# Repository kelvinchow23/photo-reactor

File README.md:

# Photoreactor Rev B

An update to the [AC-SDL4 photo-reactor](https://github.com/AC-SDL4/photo-reactor)
using custom PCBs for a four-reactor controller and interchangeable LED/fan boards.

The **photoreactor project is Rev B**. Both PCB parts remain **Rev A**:
SDL4-0001 photoreactor-controller and SDL4-0002 photoreactor-led.

- [PCB designs, BOMs, Gerbers and STEP models](electrical/README.md)
- [MicroPython test programs](firmware/README.md)
- [Wiring diagram](electrical/docs/wiring/photoreactor-wiring.pdf)
- [DigiKey import list](electrical/outputs/procurement/2026-10-15/DigiKey-bulk-import.txt)
- [Housing development](mechanical/housing/README.md)

Prototype bring-up is in progress; see [bench results](docs/bench-results.md).
Housing CAD will be added later.

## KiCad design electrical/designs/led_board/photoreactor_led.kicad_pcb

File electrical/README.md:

# Custom PCBs

PCB parts for the **Photoreactor Rev B** project. Both physical PCB revisions are
**Rev A**, dated 2026-10-08.

| Part | Native KiCad project | Fabrication and assembly files |
| --- | --- | --- |
| SDL4-0001 photoreactor-controller | [Open project](designs/controller/photoreactor_quad.kicad_pro) | [Rev A package](outputs/controller/SDL4-0001_photoreactor-controller_Rev-A_2026-10-08/) |
| SDL4-0002 photoreactor-led | [Open project](designs/led_board/photoreactor_led.kicad_pro) | [Rev A package](outputs/led_board/SDL4-0002_photoreactor-led_Rev-A_2026-10-08/) |

The controller serves four reactors. Each reactor uses two identical LED/fan
boards, linked by a custom harness. Native schematics and layouts are the design
sources; libraries are shared under `libraries/`.

## Useful files

- [Wiring diagram](docs/wiring/photoreactor-wiring.pdf) and [editable draw.io file](docs/wiring/photoreactor-wiring.drawio)
- [Controller assembly BOM](outputs/controller/SDL4-0001_photoreactor-controller_Rev-A_2026-10-08/SDL4-0001_photoreactor-controller_Rev-A_2026-10-08_BOM.csv)
- [LED-board assembly BOM](outputs/led_board/SDL4-0002_photoreactor-led_Rev-A_2026-10-08/SDL4-0002_photoreactor-led_Rev-A_2026-10-08_BOM.csv)
- [DigiKey bulk-import list](outputs/procurement/2026-10-15/DigiKey-bulk-import.txt) and [shopping guide](outputs/procurement/2026-10-15/shopping-guide.html)
- [Mechanical STEP assemblies and previews](outputs/mechanical/Rev-A/SDL4_REV_A_mechanical-models.zip)
- [Thermal guidance](docs/THERMAL_PLAN.md)
- [Bench test firmware](../firmware/README.md) and [observed results](../docs/bench-results.md)

Heatsink contact area is included in the LED mechanical model. Component envelopes
are simplified and mating plugs/wire bends require additional clearance.

## Maintenance

Helper code belongs in [automation](automation/README.md), not in design folders.
Test/export commands preserve native PCB geometry. Validation outputs go to a
separate ignored folder; existing Rev A manufacturing packages are not overwritten.

This is a functionally exercised prototype, not a thermally qualified design.

## Output naming

Release folders and deliverable filenames use
`<part-number>_<part-name>_Rev-<revision>_<YYYY-MM-DD>`, followed by the
file purpose, such as `_Gerbers.zip`, `_BOM.csv`, `_CPL.csv` or `_board-only.step`.
The date records completion of that PCB release; it is not the date of a later
file rename or documentation update. Current PCB releases were completed 2026-10-08.
Native design files and the Gerber filenames inside the fabrication ZIPs retain
their original names.

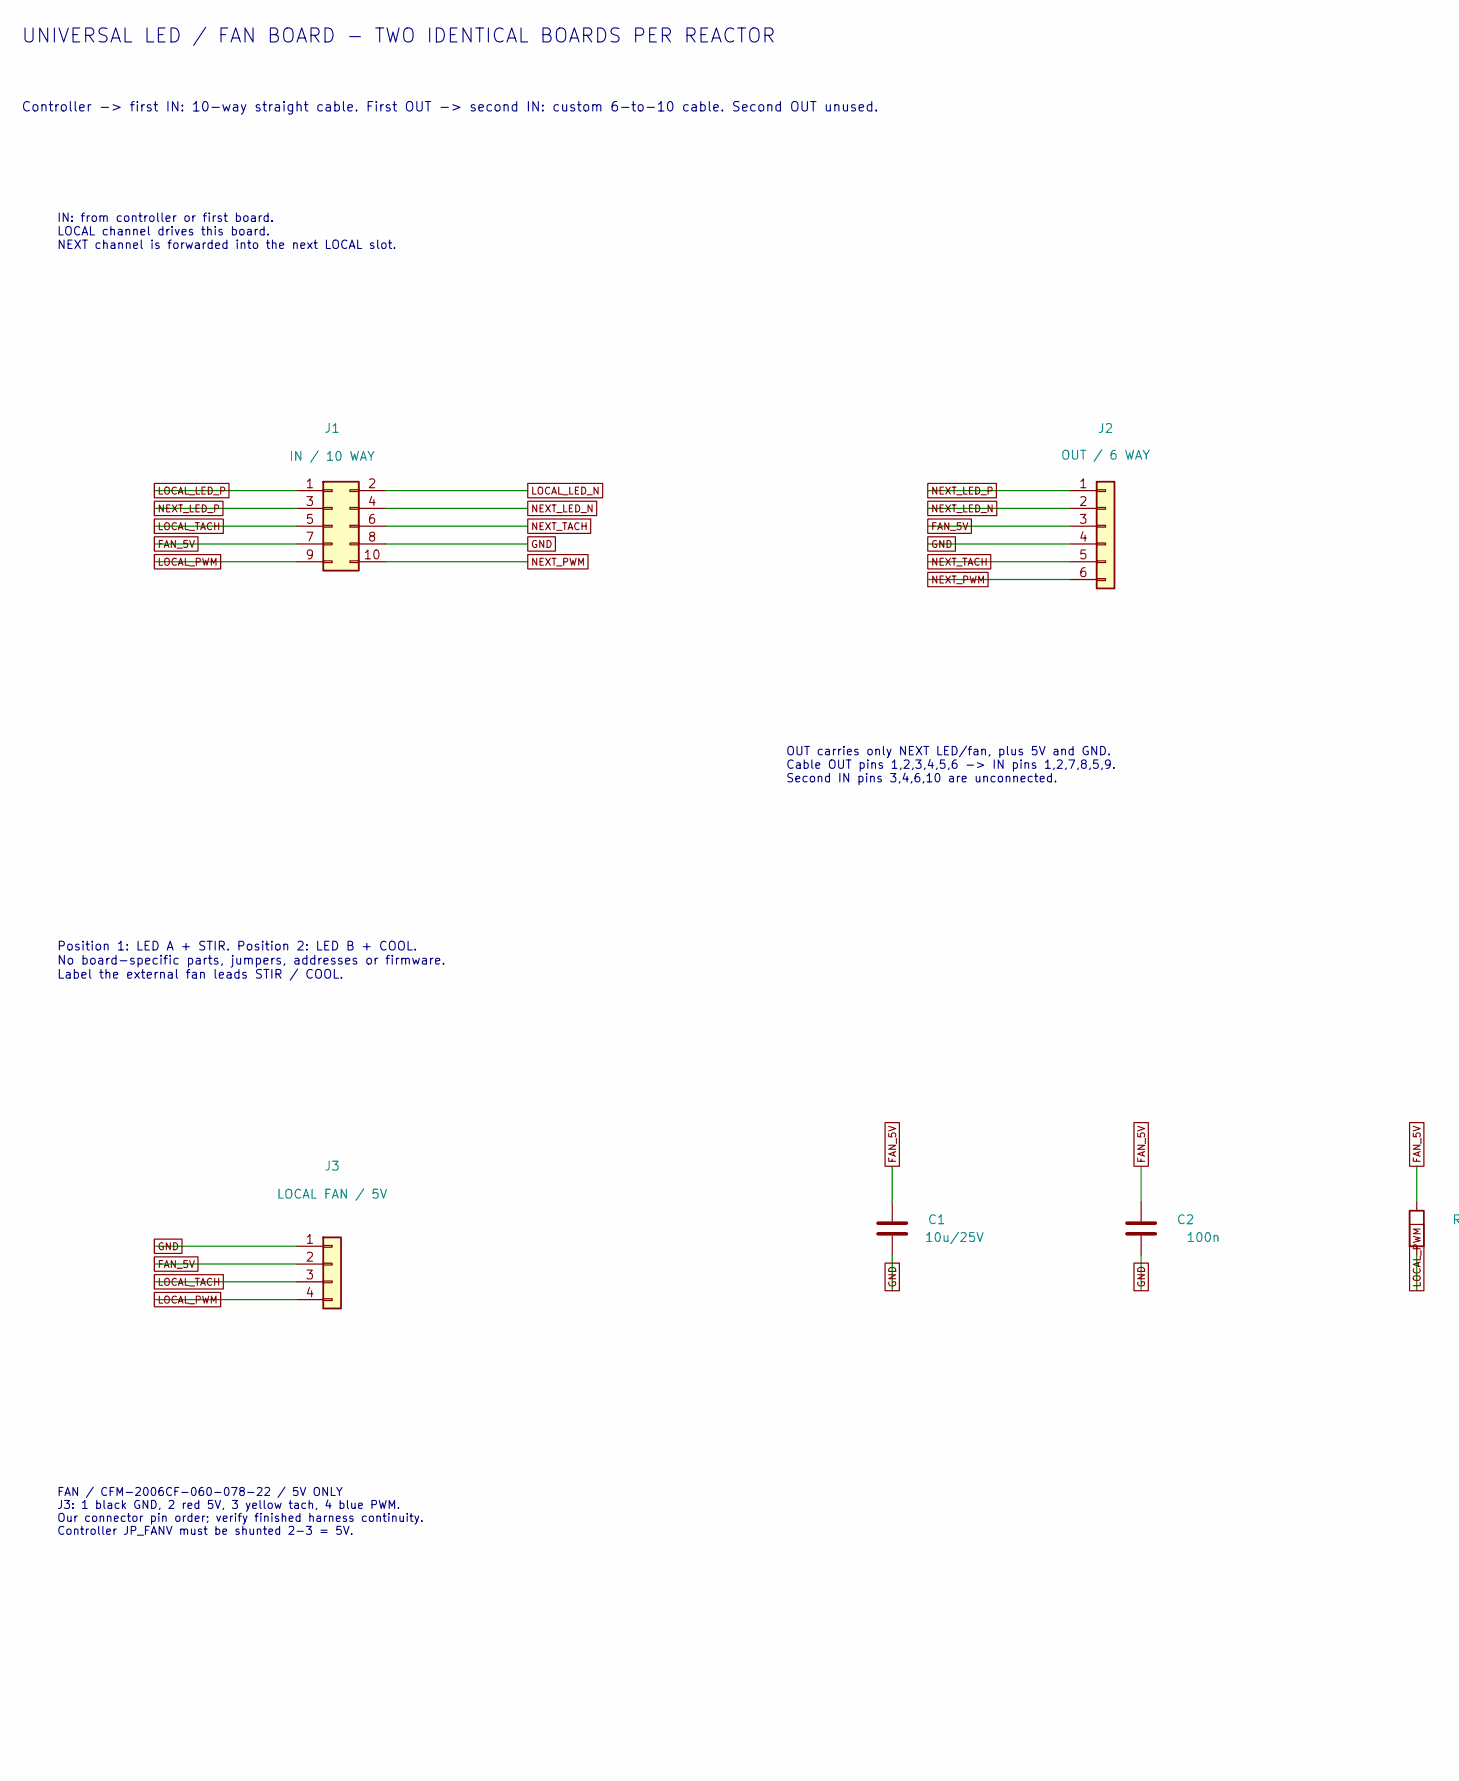
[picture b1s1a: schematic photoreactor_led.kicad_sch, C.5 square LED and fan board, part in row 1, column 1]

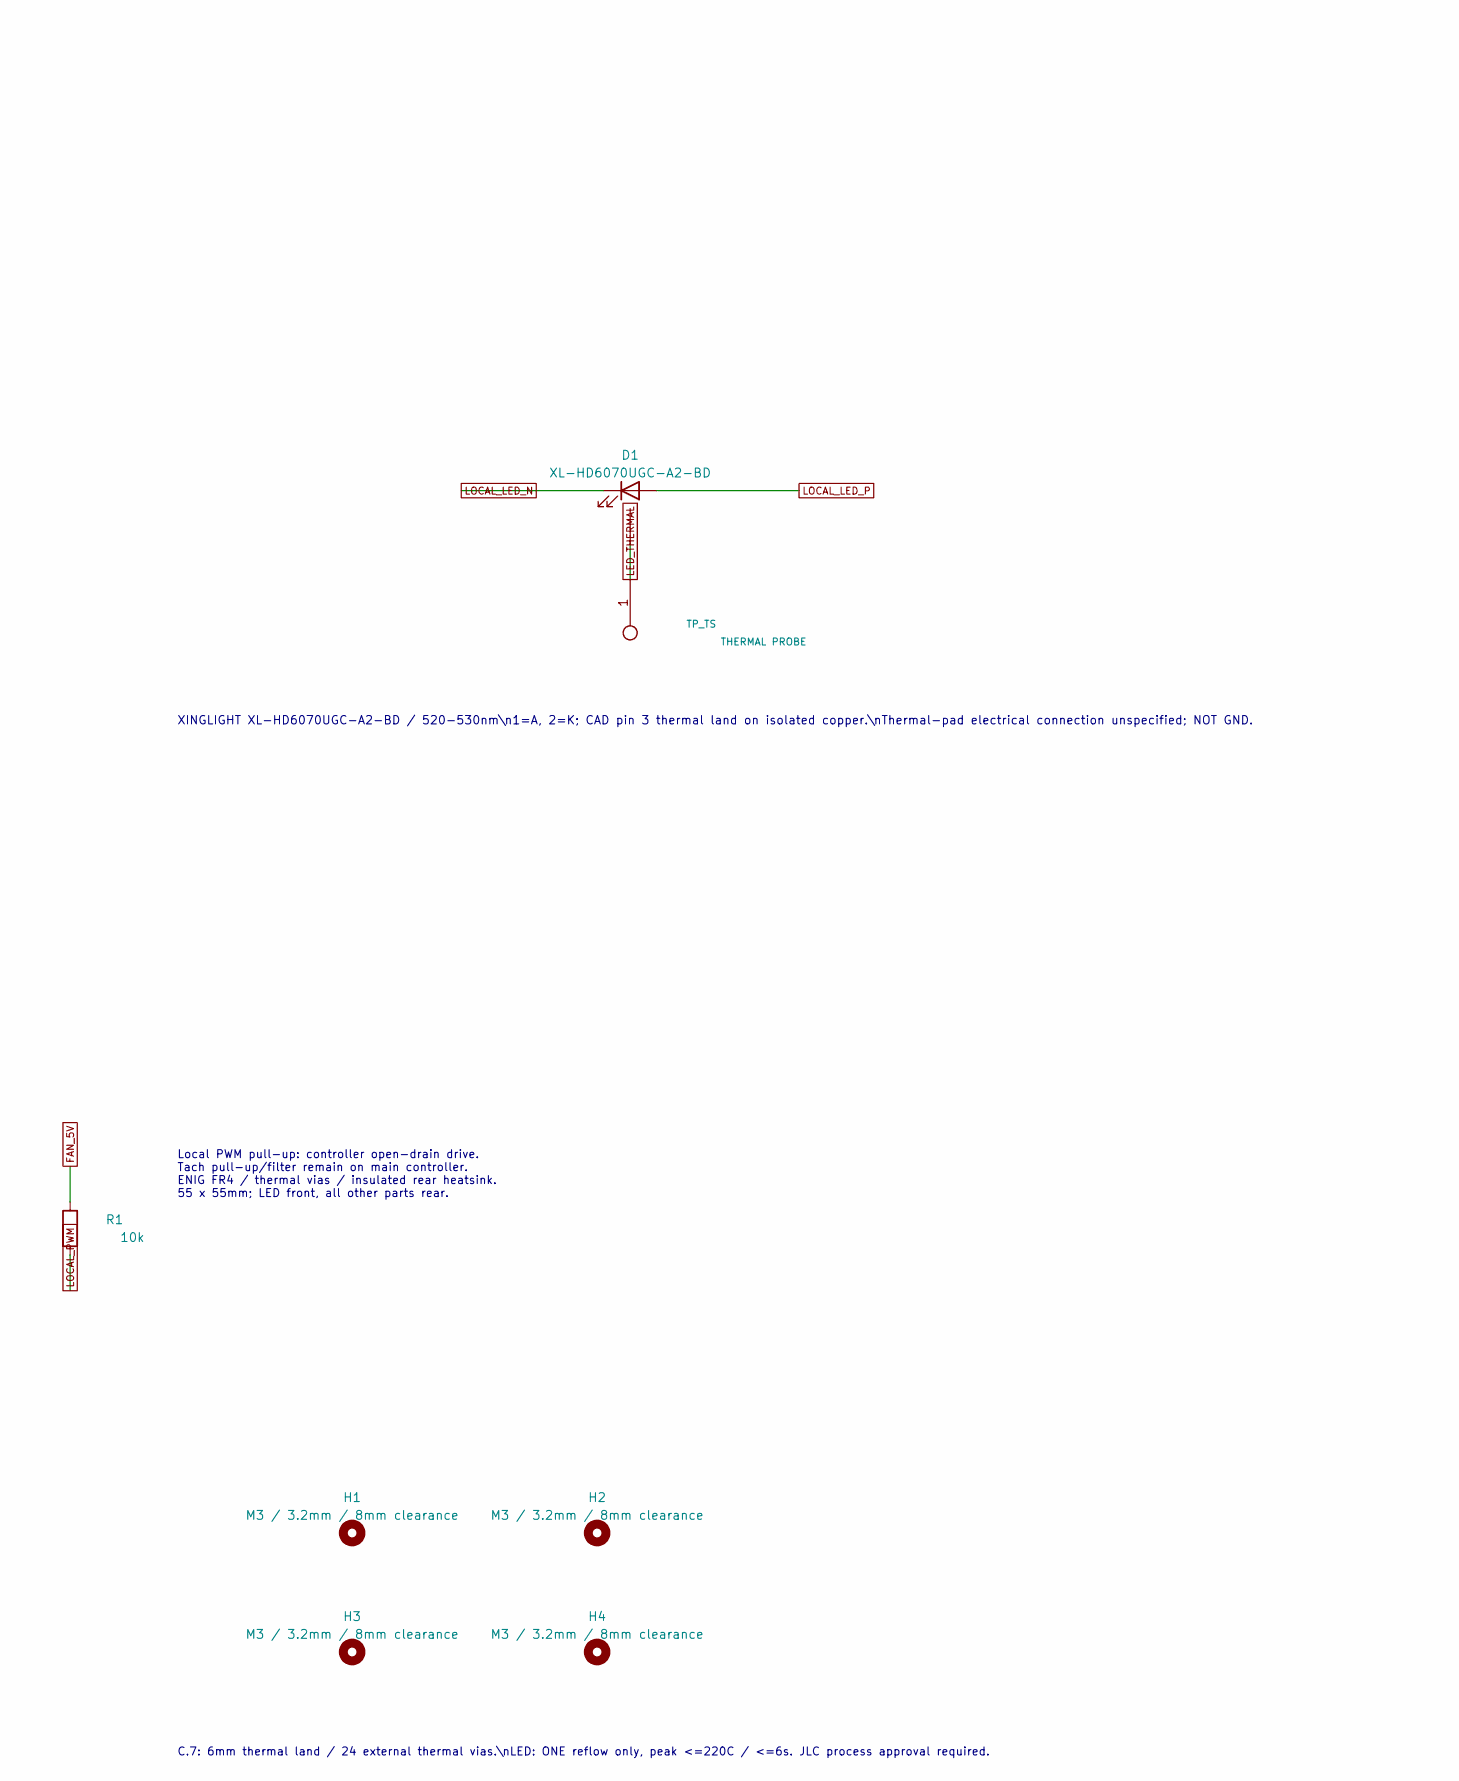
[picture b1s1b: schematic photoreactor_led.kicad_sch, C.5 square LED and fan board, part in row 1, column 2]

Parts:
C1: 10u/25V; C_0805_2012Metric; MPN CL21A106KAYNNNE
C2: 100n; C_0805_2012Metric; MPN CC0805KRX7R9BB104
D1: XL-HD6070UGC-A2-BD; LED_XINGLIGHT_XL_HD6070UGC_A2_BD; MPN XL-HD6070UGC-A2-BD
H1, H2, H3, H4: M3 / 3.2mm / 8mm clearance; MountingHole_M3_3.2mm_8mm_Clearance
J1: IN / 10 WAY; IDC-Header_2x05_P2.54mm_Vertical_SMD; MPN JXT-IDC2.54-2X5P-A2
J2: OUT / 6 WAY; JST_PH_S6B-PH-SM4-TB_1x06-1MP_P2.00mm_Horizontal; MPN S6B-PH-SM4-TB(LF)(SN)
J3: LOCAL FAN / 5V; JST_PH_S4B-PH-SM4-TB_1x04-1MP_P2.00mm_Horizontal; MPN S4B-PH-SM4-TB(LF)(SN)
R1: 10k; R_0805_2012Metric; MPN 0805W8F1002T5E
TP_TS: THERMAL PROBE; Thermal_Probe_Window

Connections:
FAN_5V: C1.1, C2.1, J1.7, J2.3, J3.2, R1.1
GND: C1.2, C2.2, J1.8, J2.4, J3.1
LED_THERMAL: D1.3 (TH), TP_TS.1
LOCAL_LED_N: D1.2 (K), J1.2
LOCAL_LED_P: D1.1 (A), J1.1
LOCAL_PWM: J1.9, J3.4, R1.2
LOCAL_TACH: J1.5, J3.3
NEXT_LED_N: J1.4, J2.2
NEXT_LED_P: J1.3, J2.1
NEXT_PWM: J1.10, J2.6
NEXT_TACH: J1.6, J2.5

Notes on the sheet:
UNIVERSAL LED / FAN BOARD - TWO IDENTICAL BOARDS PER REACTOR
Controller -> first IN: 10-way straight cable. First OUT -> second IN: custom 6-to-10 cable. Second OUT unused.
IN: from controller or first board. LOCAL channel drives this board. NEXT channel is forwarded into the next LOCAL slot.
OUT carries only NEXT LED/fan, plus 5V and GND. Cable OUT pins 1,2,3,4,5,6 -> IN pins 1,2,7,8,5,9. Second IN pins 3,4,6,10 are unconnected.
XINGLIGHT XL-HD6070UGC-A2-BD / 520-530nm\n1=A, 2=K; CAD pin 3 thermal land on isolated copper.\nThermal-pad electrical connection unspecified; NOT GND.
Position 1: LED A + STIR. Position 2: LED B + COOL. No board-specific parts, jumpers, addresses or firmware. Label the external fan leads STIR / COOL.
FAN / CFM-2006CF-060-078-22 / 5V ONLY J3: 1 black GND, 2 red 5V, 3 yellow tach, 4 blue PWM. Our connector pin order; verify finished harness continuity. Controller JP_FANV must be shunted 2-3 = 5V.
Local PWM pull-up: controller open-drain drive. Tach pull-up/filter remain on main controller. ENIG FR4 / thermal vias / insulated rear heatsink. 55 x 55mm; LED front, all other parts rear.
C.7: 6mm thermal land / 24 external thermal vias.\nLED: ONE reflow only, peak <=220C / <=6s. JLC process approval required.

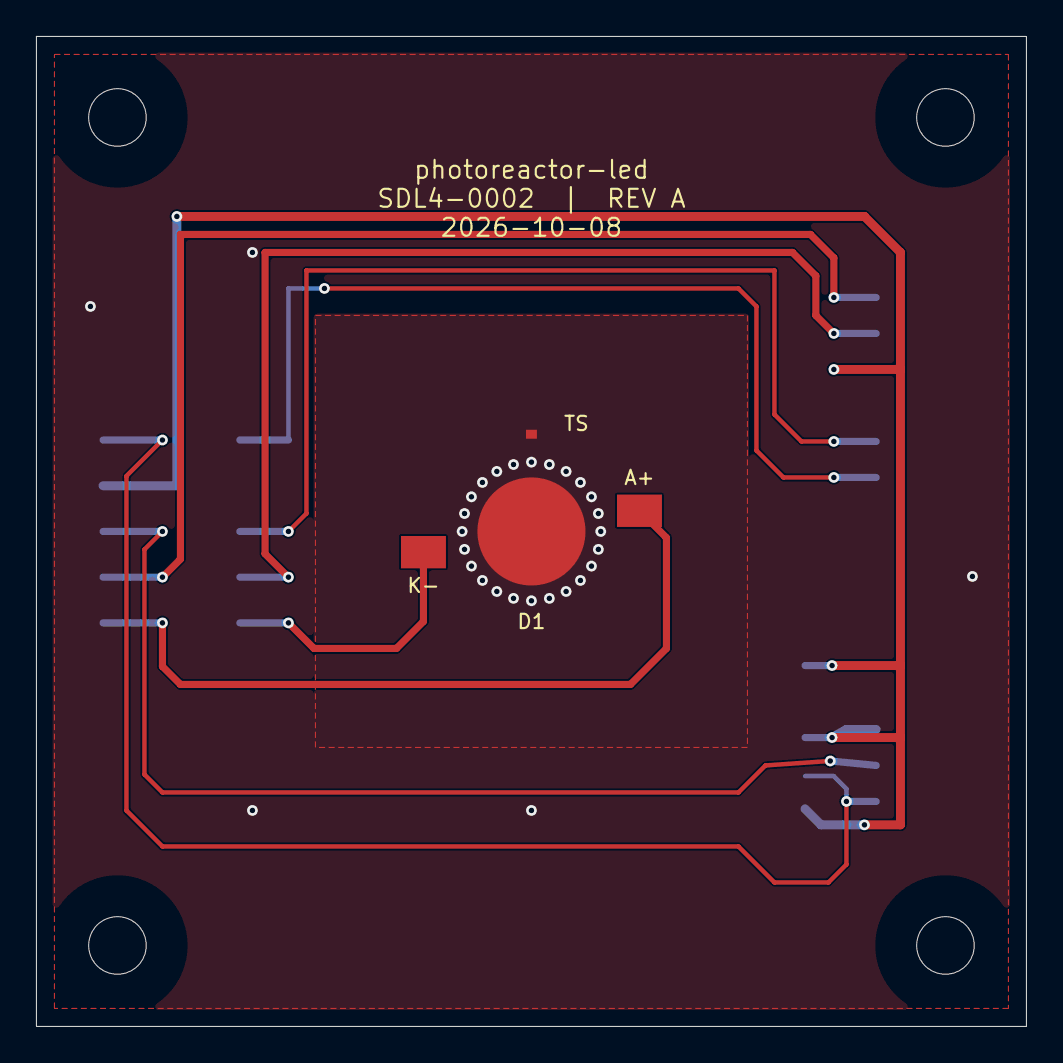
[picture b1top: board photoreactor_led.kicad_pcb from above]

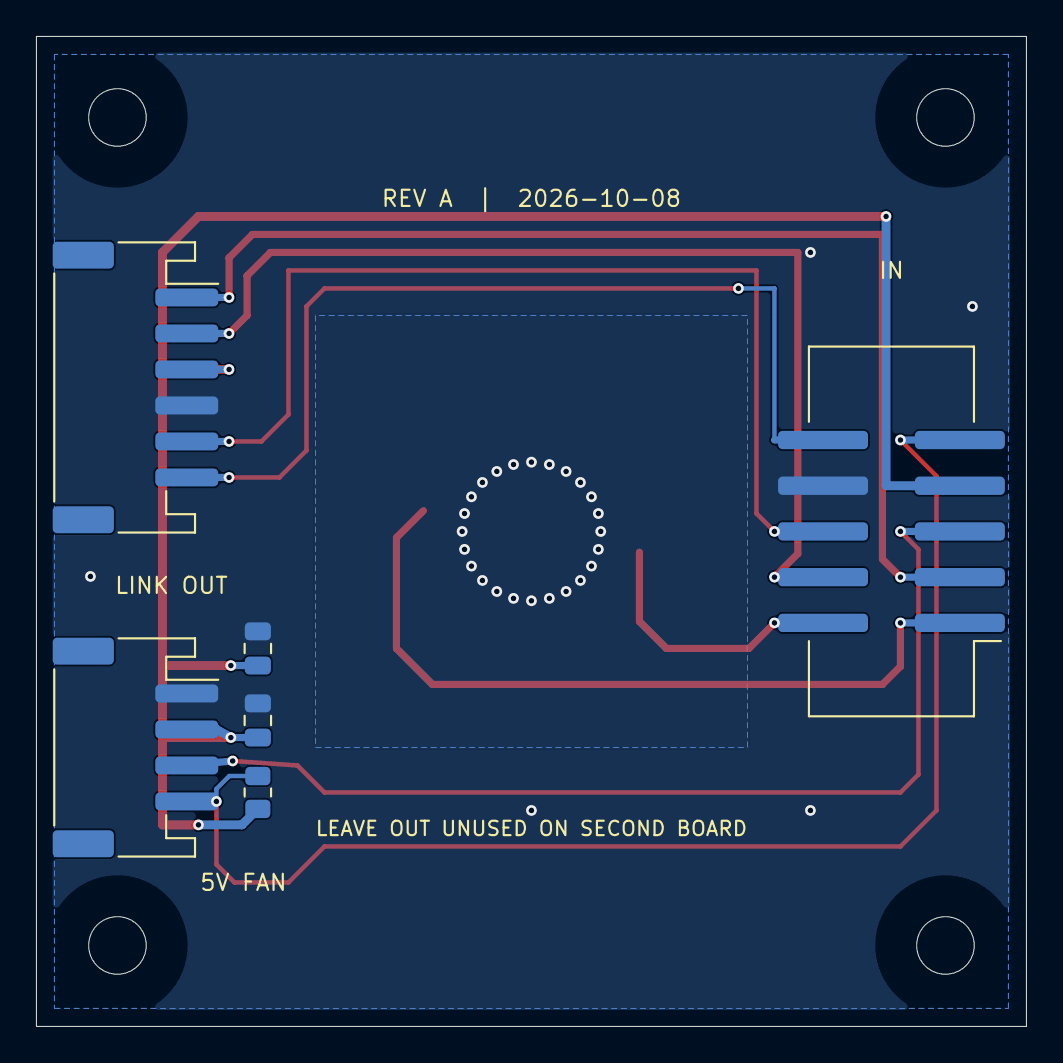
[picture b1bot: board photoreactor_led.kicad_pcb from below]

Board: 2 copper layers, 55.0 x 55.0 mm, 12 parts (6 on the bottom side), 11 nets.

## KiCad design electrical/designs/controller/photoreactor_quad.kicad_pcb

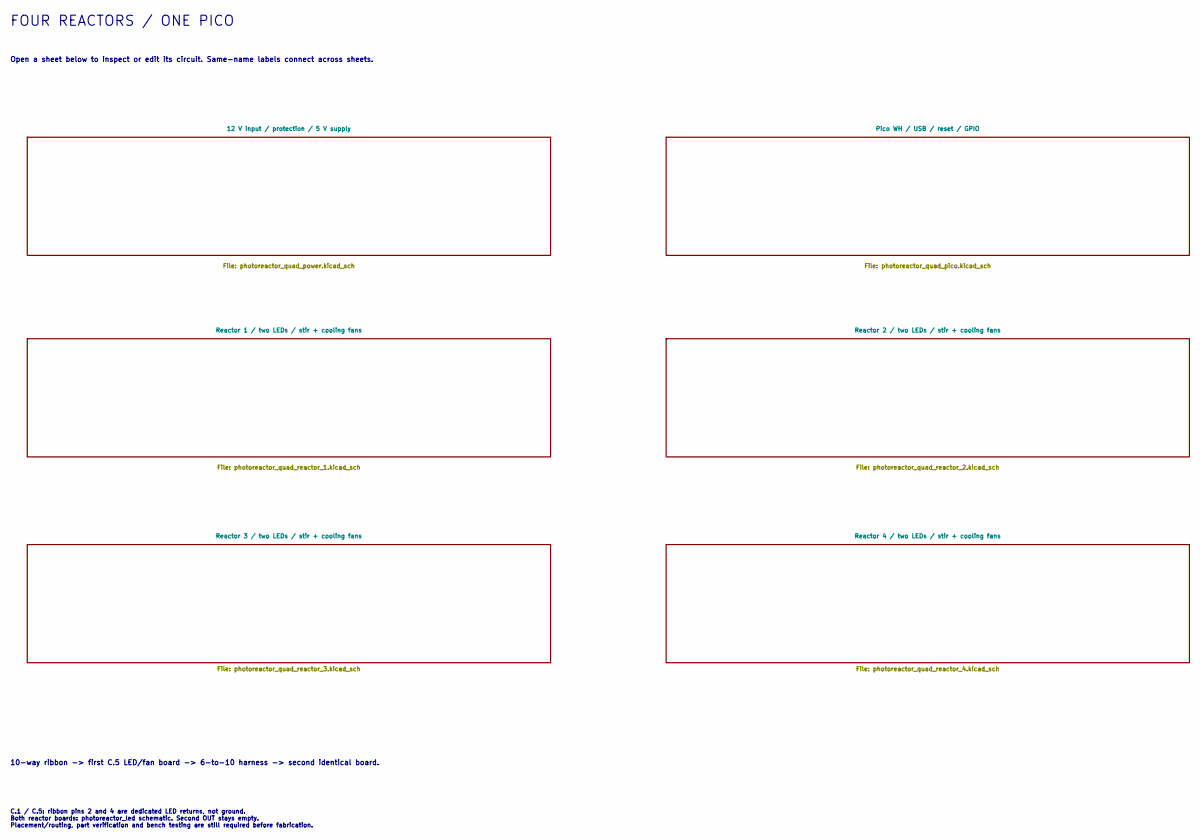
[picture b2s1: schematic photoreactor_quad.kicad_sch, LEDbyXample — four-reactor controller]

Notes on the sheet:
FOUR REACTORS / ONE PICO
Open a sheet below to inspect or edit its circuit. Same-name labels connect across sheets.
10-way ribbon -> first C.5 LED/fan board -> 6-to-10 harness -> second identical board.
C.1 / C.5: ribbon pins 2 and 4 are dedicated LED returns, not ground. Both reactor boards: photoreactor_led schematic. Second OUT stays empty. Placement/routing, part verification and bench testing are still required before fabrication.

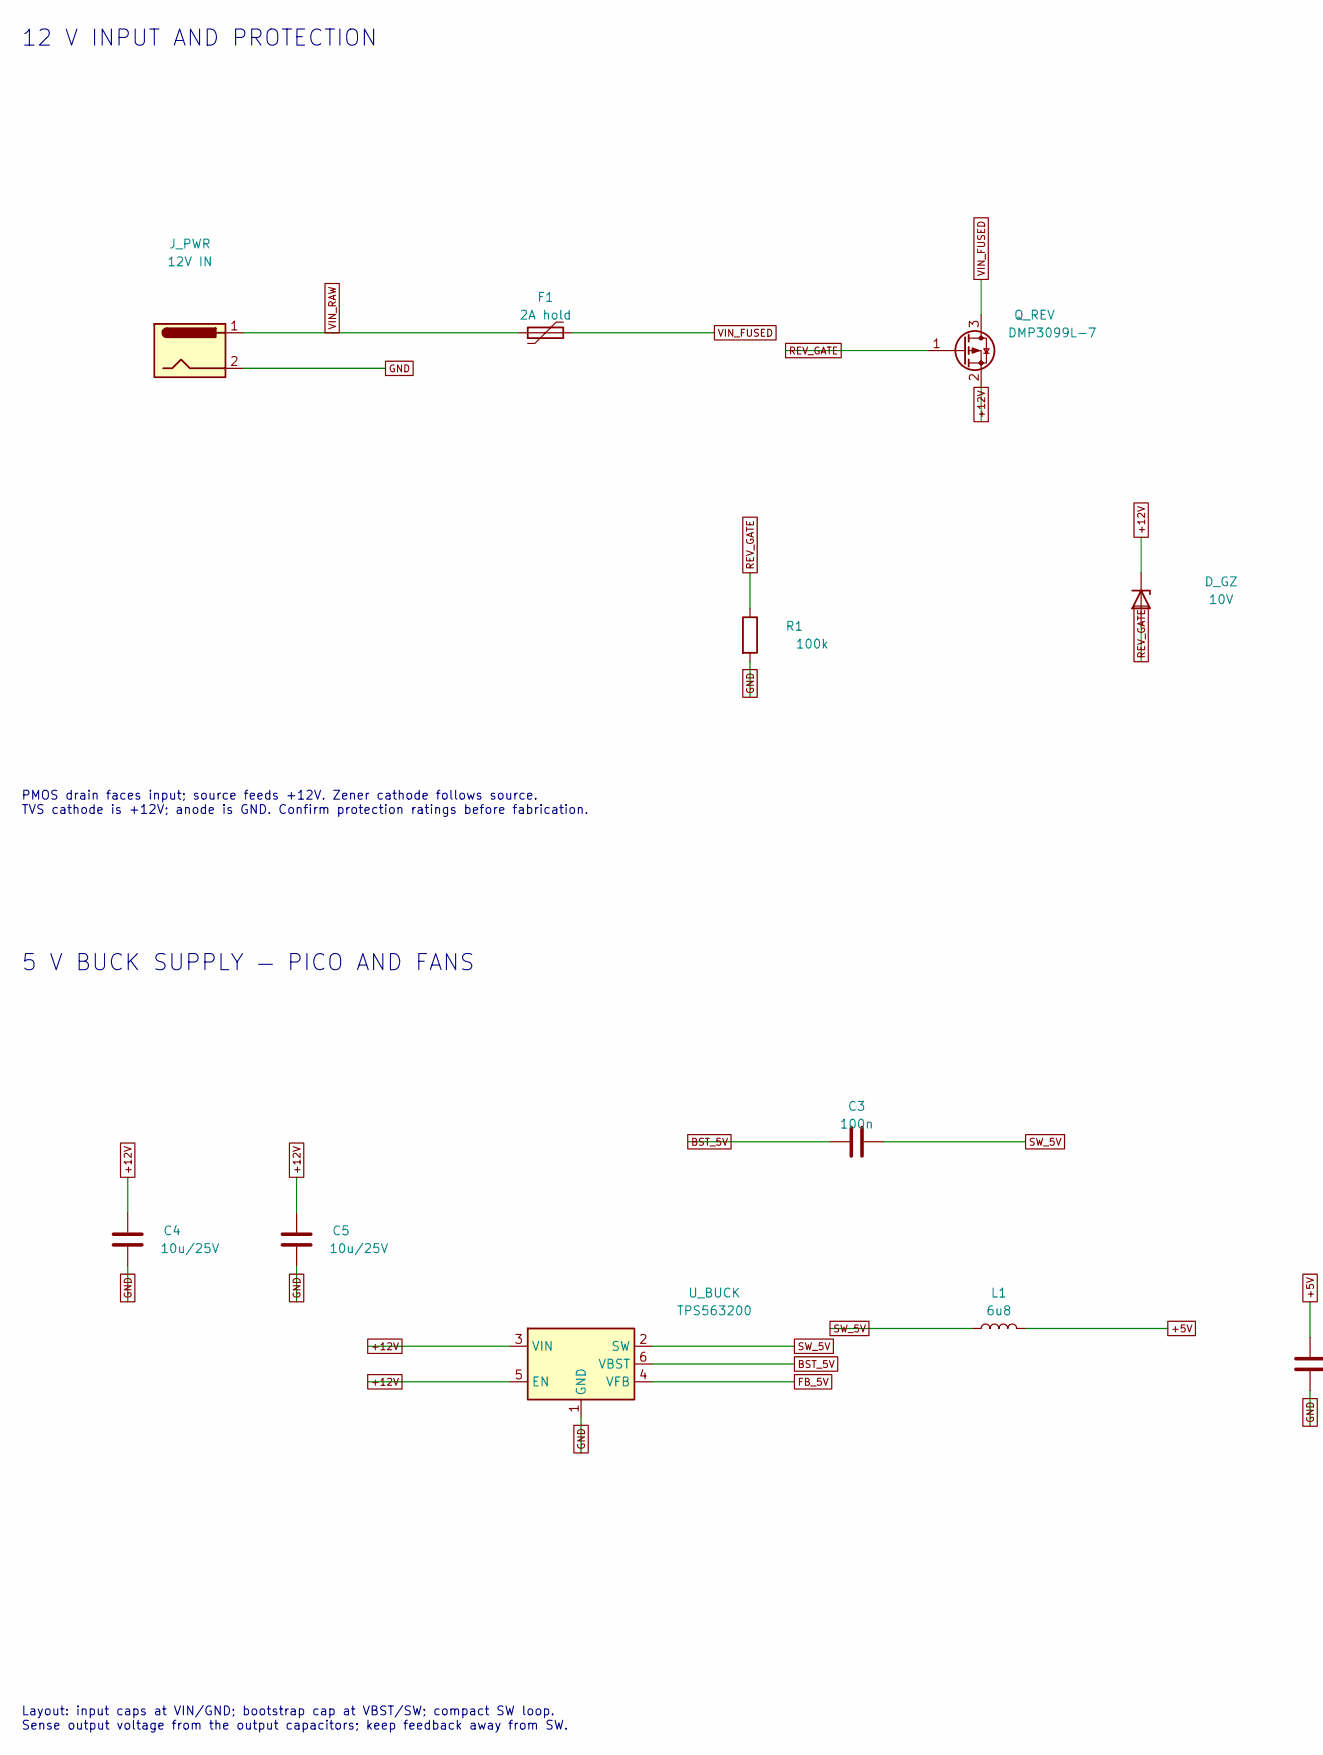
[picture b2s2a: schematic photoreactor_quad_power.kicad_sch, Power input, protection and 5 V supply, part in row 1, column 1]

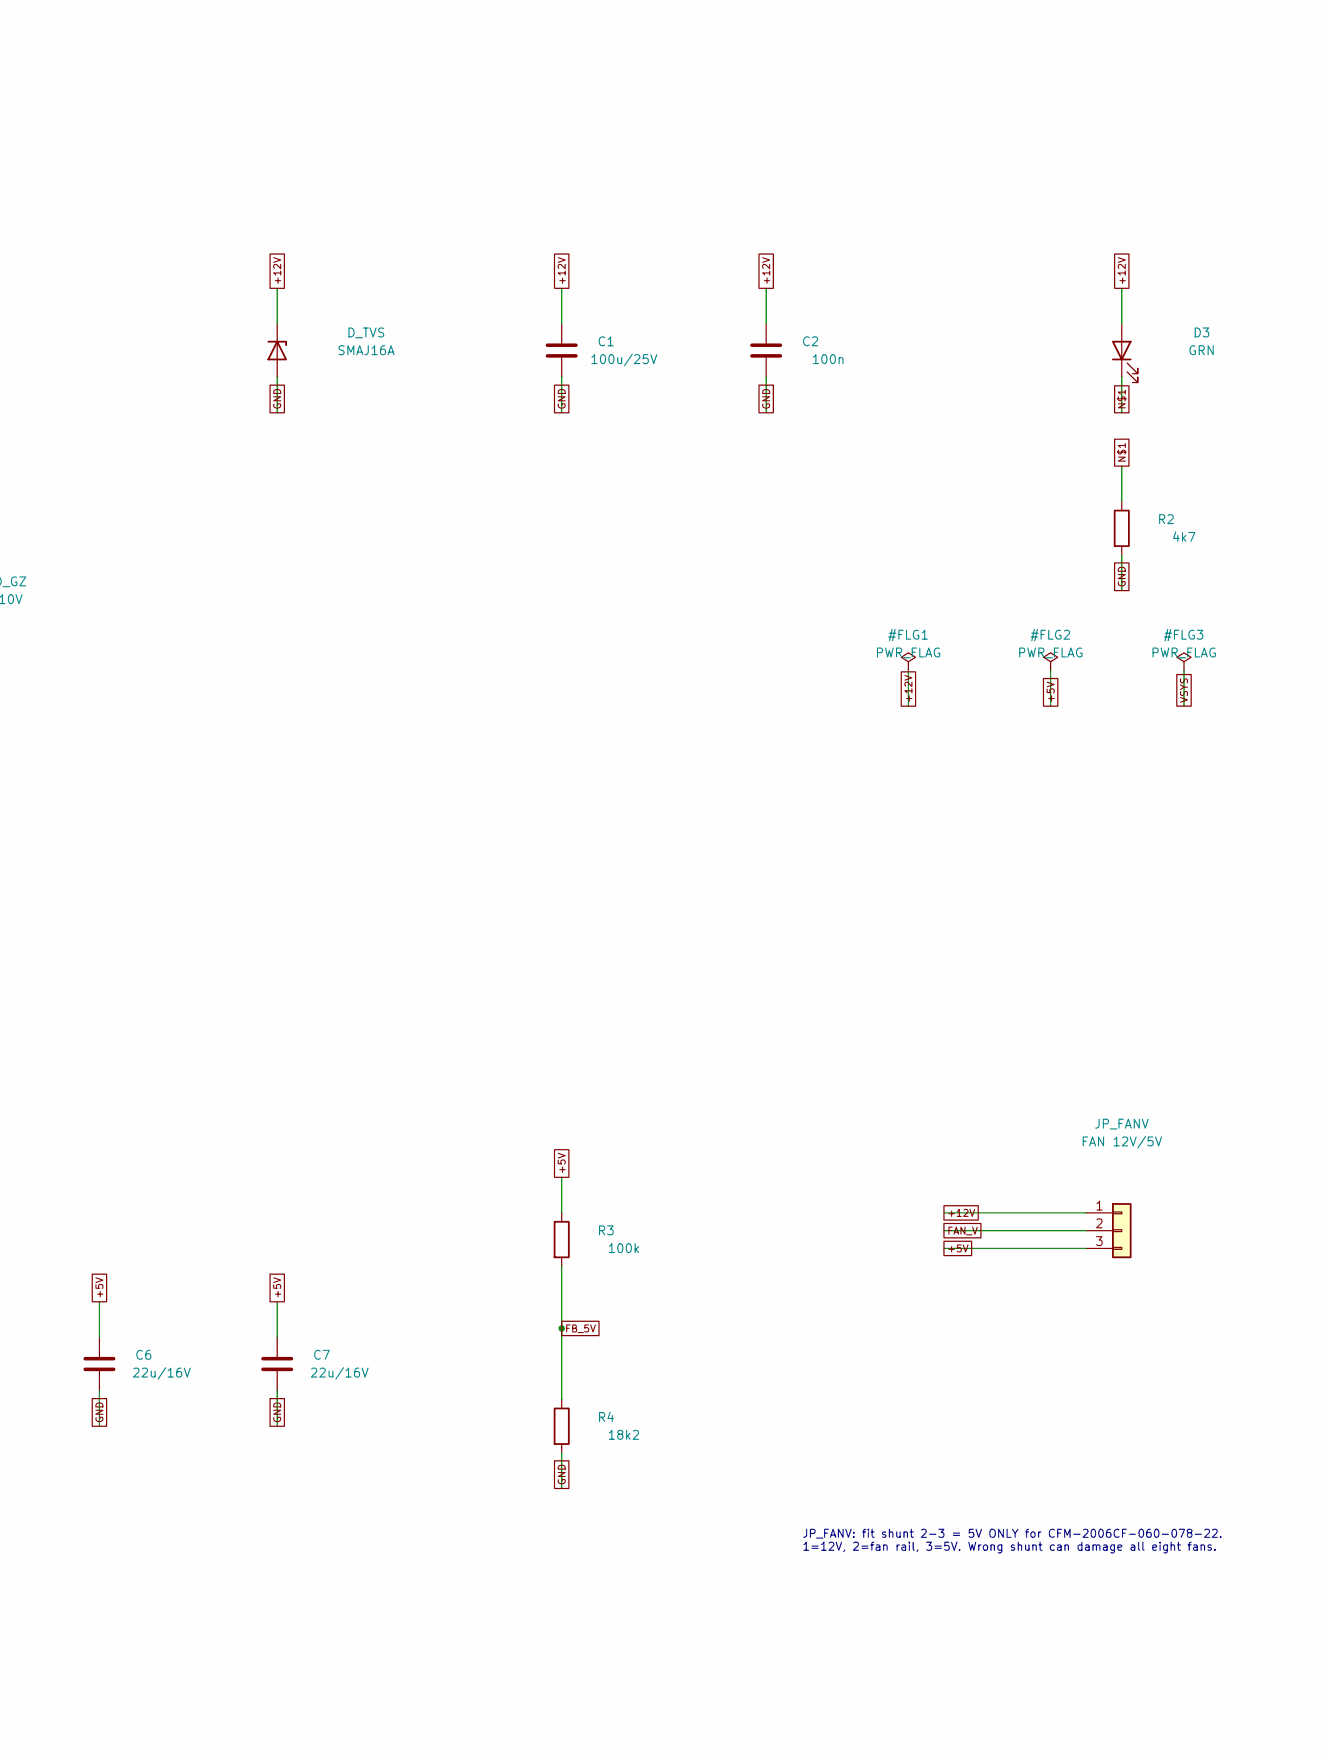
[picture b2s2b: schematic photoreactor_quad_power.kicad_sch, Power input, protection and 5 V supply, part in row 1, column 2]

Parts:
C1: 100u/25V; CP_Elec_6.3x7.7_ControllerSilk; MPN UWT1E101MCL1GS
C2, C3: 100n; C_0805_2012Metric; MPN CC0805KRX7R9BB104; LCSC C49678
C4, C5: 10u/25V; C_0805_2012Metric; MPN CL21A106KAYNNNE; LCSC C15850
C6, C7: 22u/16V; C_1210_3225Metric; MPN TCC1210X7R226K250MT; LCSC C49118556
D3: GRN; LED_0805_2012Metric; MPN KT-0805G; LCSC C2297
D_GZ: 10V; D_SOD-123; MPN MMSZ5240B
D_TVS: SMAJ16A; D_SMA; MPN SMAJ16A
F1: 2A hold; R_1812_4532Metric; MPN 1812L200/16DR; LCSC C439873
JP_FANV: FAN 12V/5V; Samtec_TSM-103_SV; MPN TSM-103-01-L-SV-TR; LCSC C7074494
J_PWR: 12V IN; BarrelJack_Wuerth_6941xx301002; MPN 694106301002
L1: 6u8; L_Bourns_SRN6045TA; MPN SRN6045TA-6R8M
Q_REV: DMP3099L-7; SOT-23; MPN DMP3099L-7
R1, R3: 100k; R_0805_2012Metric; MPN 0805W8F1003T5E; LCSC C149504
R2: 4k7; R_0805_2012Metric; MPN 0805W8F4701T5E; LCSC C17673
R4: 18k2; R_0805_2012Metric; MPN RC0805FR-0718K2L; LCSC C483023
U_BUCK: TPS563200; SOT-23-6; MPN TPS563200DDCR

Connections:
+5V: C6.1, C7.1, JP_FANV.3, L1.2, R3.1; also elsewhere on the board
+12V: C1.1, C2.1, C4.1, C5.1, D3.2 (A), D_GZ.1 (K), D_TVS.1 (K), JP_FANV.1, Q_REV.2 (S), U_BUCK.3 (VIN), U_BUCK.5 (EN); also elsewhere on the board
BST_5V: C3.1, U_BUCK.6 (VBST)
FAN_V: JP_FANV.2; also elsewhere on the board
FB_5V: R3.2, R4.1, U_BUCK.4 (VFB)
GND: C1.2, C2.2, C4.2, C5.2, C6.2, C7.2, D_TVS.2 (A), J_PWR.2, R1.2, R2.2, R4.2, U_BUCK.1 (GND); also elsewhere on the board
unnamed: D3.1 (K), R2.1
REV_GATE: D_GZ.2 (A), Q_REV.1 (G), R1.1
SW_5V: C3.2, L1.1, U_BUCK.2 (SW)
VIN_FUSED: F1.2, Q_REV.3 (D)
VIN_RAW: F1.1, J_PWR.1

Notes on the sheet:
12 V INPUT AND PROTECTION
PMOS drain faces input; source feeds +12V. Zener cathode follows source. TVS cathode is +12V; anode is GND. Confirm protection ratings before fabrication.
5 V BUCK SUPPLY — PICO AND FANS
JP_FANV: fit shunt 2-3 = 5V ONLY for CFM-2006CF-060-078-22. 1=12V, 2=fan rail, 3=5V. Wrong shunt can damage all eight fans.
Layout: input caps at VIN/GND; bootstrap cap at VBST/SW; compact SW loop. Sense output voltage from the output capacitors; keep feedback away from SW.

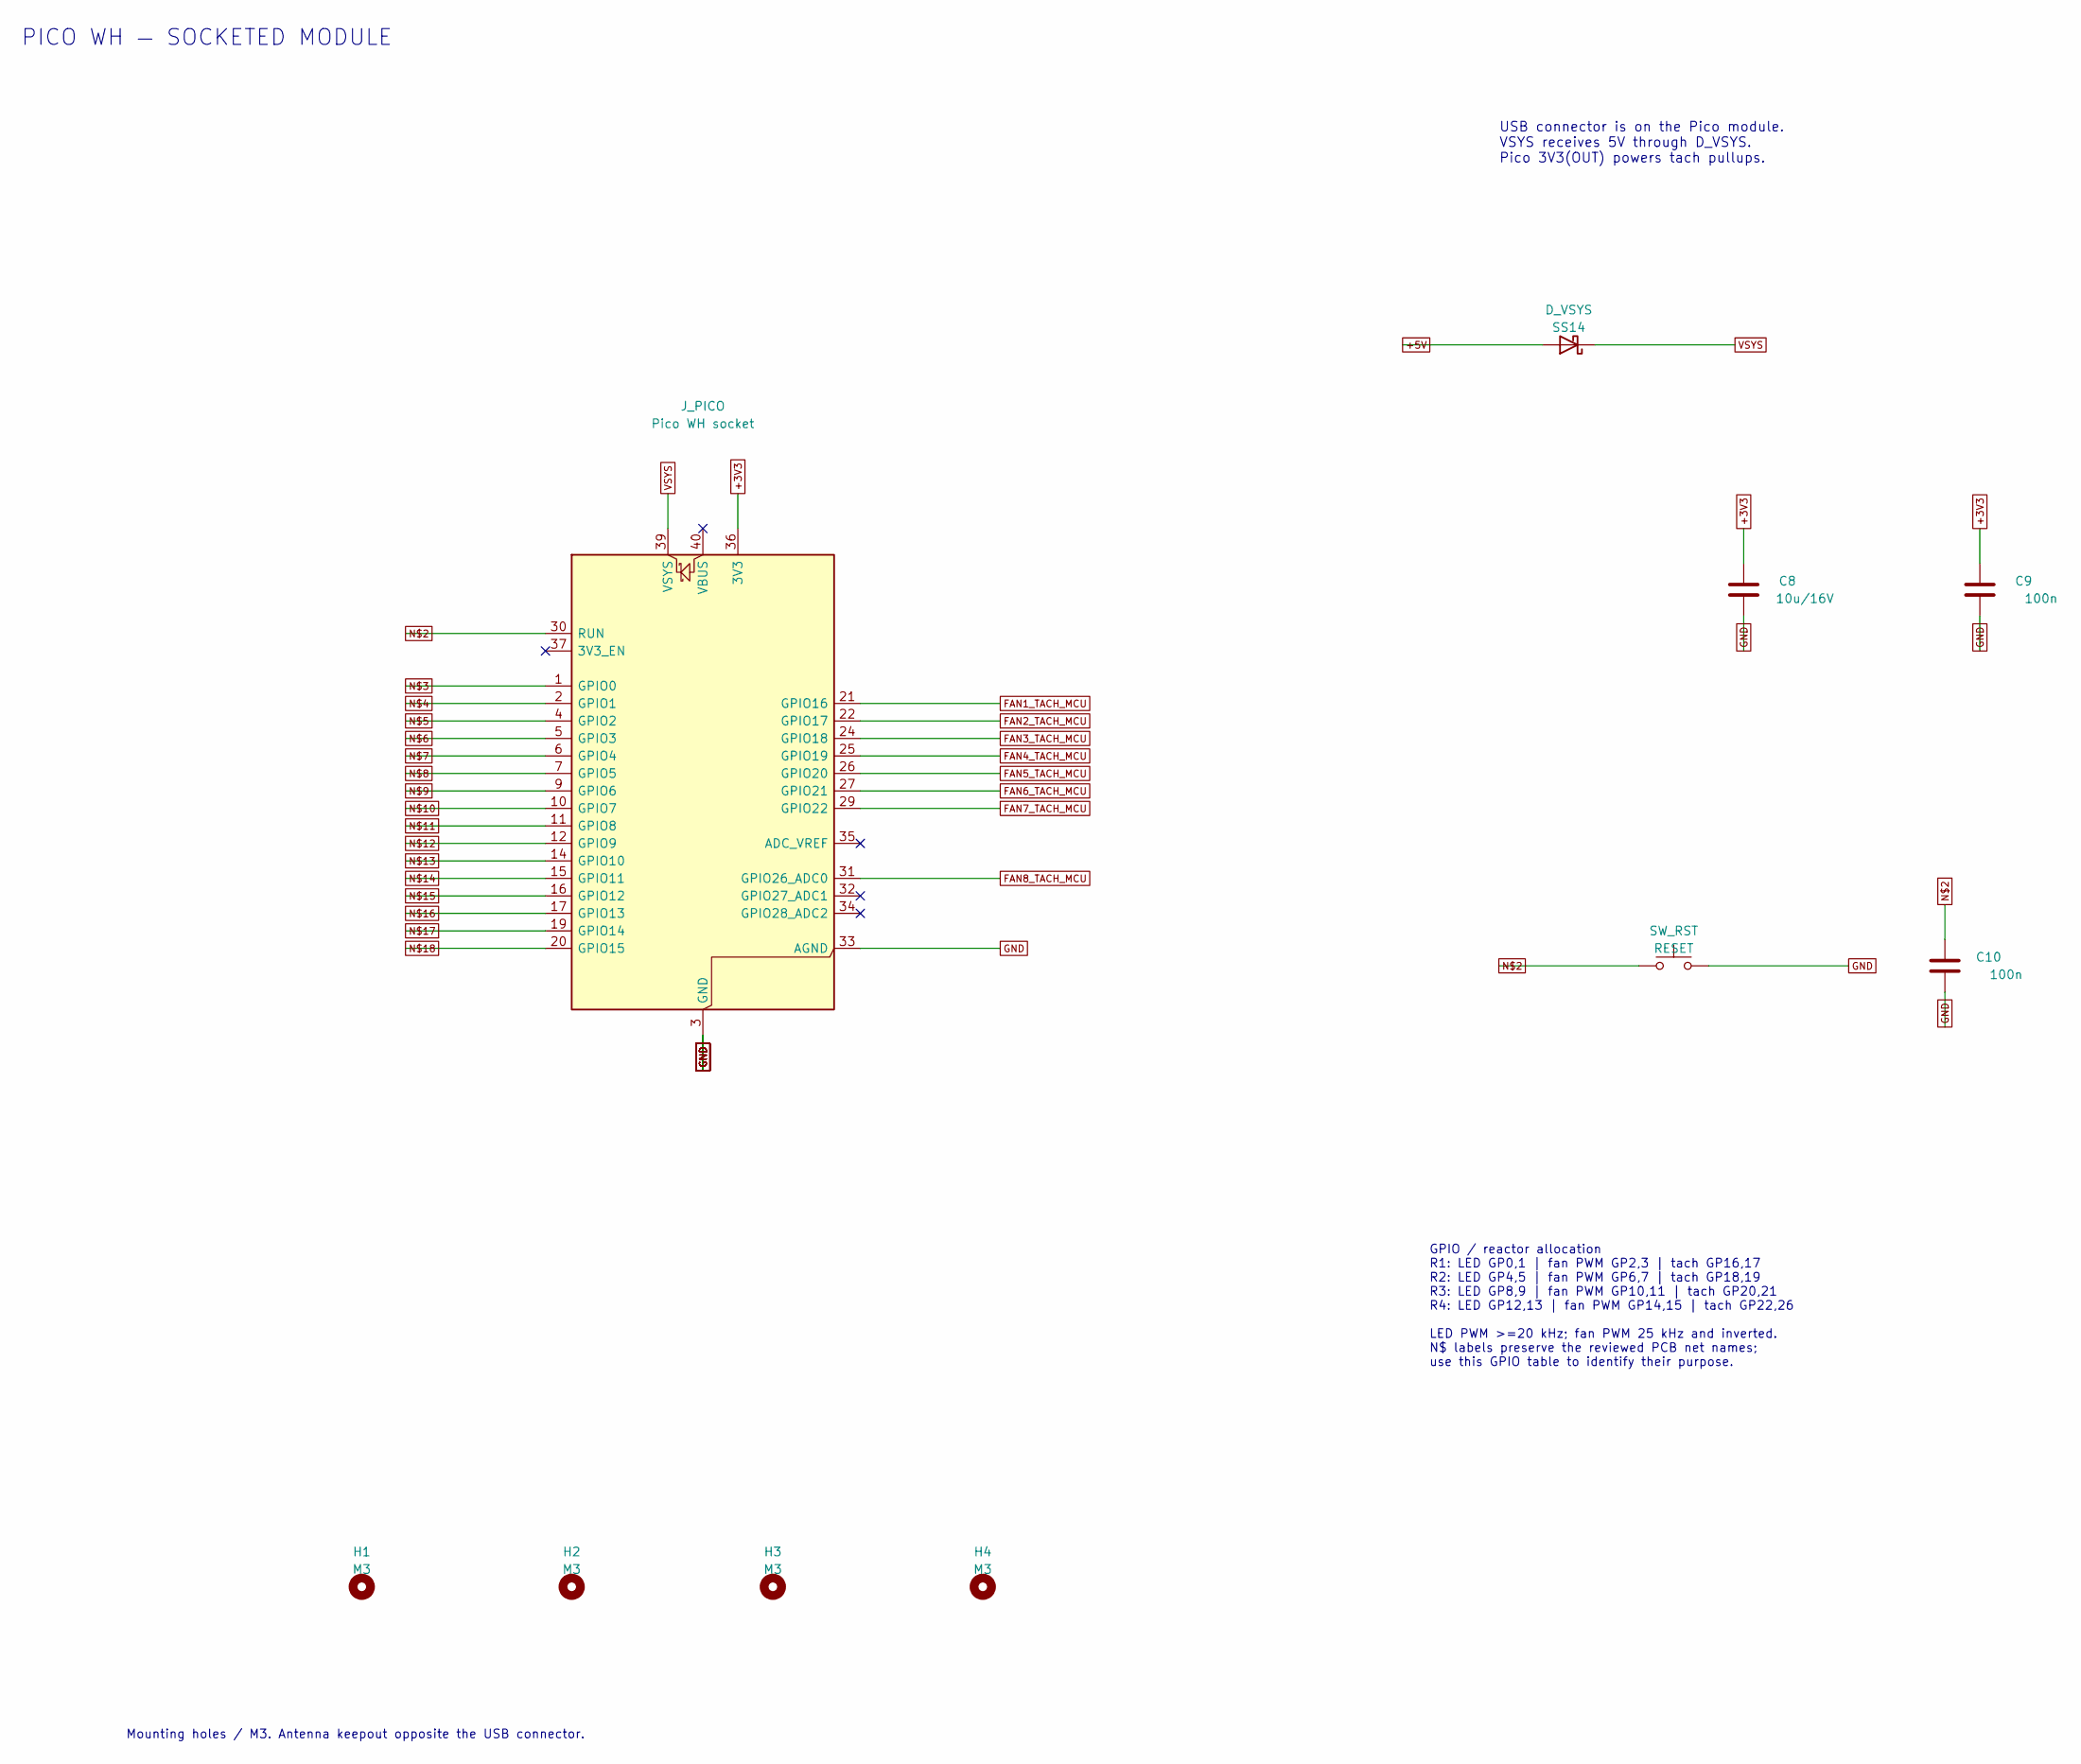
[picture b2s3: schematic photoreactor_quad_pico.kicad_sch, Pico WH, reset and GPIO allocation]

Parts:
C8: 10u/16V; C_0805_2012Metric; MPN CL21A106KAYNNNE; LCSC C15850
C9, C10: 100n; C_0805_2012Metric; MPN CC0805KRX7R9BB104; LCSC C49678
D_VSYS: SS14; D_SMA; MPN SS14
H1, H2, H3, H4: M3; MountingHole_3.2mm_M3_Pad
J_PICO: Pico WH socket; RPi_Pico_Socket_2x20_P2.54mm_Row17.78mm
SW_RST: RESET; SW_SPST_PTS645Sx43SMTR92; MPN PTS645SK43SMTR92LFS; LCSC C221871

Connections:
+3V3: C8.1, C9.1, J_PICO.36 (3V3); also elsewhere on the board
+5V: D_VSYS.2 (A); also elsewhere on the board
FAN1_TACH_MCU: J_PICO.21 (GPIO16); also elsewhere on the board
FAN2_TACH_MCU: J_PICO.22 (GPIO17); also elsewhere on the board
FAN3_TACH_MCU: J_PICO.24 (GPIO18); also elsewhere on the board
FAN4_TACH_MCU: J_PICO.25 (GPIO19); also elsewhere on the board
FAN5_TACH_MCU: J_PICO.26 (GPIO20); also elsewhere on the board
FAN6_TACH_MCU: J_PICO.27 (GPIO21); also elsewhere on the board
FAN7_TACH_MCU: J_PICO.29 (GPIO22); also elsewhere on the board
FAN8_TACH_MCU: J_PICO.31 (GPIO26_ADC0); also elsewhere on the board
GND: C8.2, C9.2, C10.2, J_PICO.3 (GND), J_PICO.8 (GND), J_PICO.13 (GND), J_PICO.18 (GND), J_PICO.23 (GND), J_PICO.28 (GND), J_PICO.33 (AGND), J_PICO.38 (GND), SW_RST.2; also elsewhere on the board
unnamed: C10.1, J_PICO.30 (RUN), SW_RST.1
unnamed 73: J_PICO.1 (GPIO0); also elsewhere on the board
unnamed 74: J_PICO.2 (GPIO1); also elsewhere on the board
unnamed 75: J_PICO.4 (GPIO2); also elsewhere on the board
unnamed 76: J_PICO.5 (GPIO3); also elsewhere on the board
unnamed 77: J_PICO.6 (GPIO4); also elsewhere on the board
unnamed 78: J_PICO.7 (GPIO5); also elsewhere on the board
unnamed 79: J_PICO.9 (GPIO6); also elsewhere on the board
unnamed 80: J_PICO.10 (GPIO7); also elsewhere on the board
unnamed 81: J_PICO.11 (GPIO8); also elsewhere on the board
unnamed 82: J_PICO.12 (GPIO9); also elsewhere on the board
unnamed 83: J_PICO.14 (GPIO10); also elsewhere on the board
unnamed 84: J_PICO.15 (GPIO11); also elsewhere on the board
unnamed 85: J_PICO.16 (GPIO12); also elsewhere on the board
unnamed 86: J_PICO.17 (GPIO13); also elsewhere on the board
unnamed 87: J_PICO.19 (GPIO14); also elsewhere on the board
unnamed 88: J_PICO.20 (GPIO15); also elsewhere on the board
VSYS: D_VSYS.1 (K), J_PICO.39 (VSYS)

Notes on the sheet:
PICO WH — SOCKETED MODULE
USB connector is on the Pico module. VSYS receives 5V through D_VSYS. Pico 3V3(OUT) powers tach pullups.
GPIO / reactor allocation R1: LED GP0,1 | fan PWM GP2,3 | tach GP16,17 R2: LED GP4,5 | fan PWM GP6,7 | tach GP18,19 R3: LED GP8,9 | fan PWM GP10,11 | tach GP20,21 R4: LED GP12,13 | fan PWM GP14,15 | tach GP22,26 LED PWM >=20 kHz; fan PWM 25 kHz and inverted. N$ labels preserve the reviewed PCB net 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
Mounting holes / M3. Antenna keepout opposite the USB connector.
